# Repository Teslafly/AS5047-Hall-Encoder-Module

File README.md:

# AS5047-Hall-Encoder-Module
Mini breakout Board for the AS5047 Hall Encoder chip. Works with Vesc

this project is made with kicad nightly 5.99. if it doesn't open with the latest kicad version, it will with `Version: (5.99.0-9885-g7a8abcadd2), release build`

!!readme not finished!!

pcb manufacture:
jlcpcbb did a good job and was able to route out the pcb's without mousebites or such.

bom:
digikey/mouser:

lcsc:

conneccctors:
make your own cable:

recommended crimpers:

lcsc connectors:

digikey/mouser connectors:

6 pin cable:
https://www.ebay.com/itm/184222360204?var=691936123738

if you hate crimping, there are prebuilt pigtails you can use to make short runs or cut up to make your own cable.
prebuilt pigtail source:
https://www.ebay.com/itm/114555495221?hash=item1aac0a2335:g:jwIAAOSwGsVaQia0
https://www.aliexpress.com/item/4000699606111.html

(need jst ph source)

# mounting:
 I recommend using nylon m3 screws. like ((xxlinkxxx)). steel screws may disrupt the magnetic feild and affect sensing. they also are non conductive and non marring. while the pcb has been designed to route signals away from under both sides of the screw holes, ther copper ground plane is still present under the screws. screws can be mounted from either side of the board. if mounting directly to metal, it is recommended to put a nylon washer or other piece of plastic between the metal and pcb.

if you have access to a 3d printer. designing a 3d printed mount for this board is likely the easiest route if there is nalready not a good mounting loccation.
provide a example 3d printed mount for each side?

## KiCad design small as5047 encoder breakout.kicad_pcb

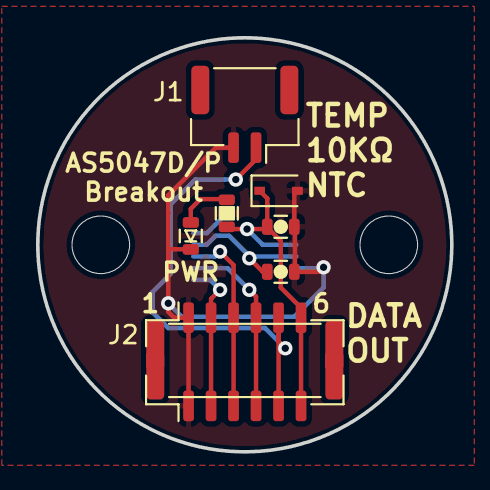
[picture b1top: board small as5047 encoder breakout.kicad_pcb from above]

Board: 2 copper layers, 23.0 x 23.0 mm, 11 parts (1 on the bottom side), 7 nets.

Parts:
C1: 4.7uF; C_0603
C2: 1uF; C_0603
D1: BLUE LED; D_0603
D2: SD05-01FTG; D_SOD-323
H1, H2: MountingHole; MountingHole_3.2mm_M3
J1: Conn_01x02; JST_GH_SM02B-GHS-TB_1x02-1MP_P1.25mm_Horizontal
J2: Conn_01x06; JST_GH_BM06B-GHS-TBT_1x06-1MP_P1.25mm_Vertical
J3: Conn_01x06; JST_GH_SM06B-GHS-TB_1x06-1MP_P1.25mm_Horizontal
R1: 10K; R_0603
U1: AS5047P; TSSOP-14_4.4x5mm_P0.65mm

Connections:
+3V3: C2.1, U1.4 (MOSI), U1.12 (VDD3V3)
+5V: C1.1, D2.1 (K), J2.6, J3.6, R1.1, U1.11 (VDD)
/H1/SCK: J2.4, J3.4, U1.2 (CLK)
/H2/MISO: J2.3, J3.3, U1.3 (MISO)
/H3/CS: J2.2, J3.2, U1.1 (~CS)
/Temp: J1.1, J2.5, J3.5
GND: C1.2, C2.2, D2.2 (A), J1.2, J2.1, J3.1, U1.5 (TST), U1.13 (GND)

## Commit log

2021-05-16 full working pcb
2021-05-16 add readme links
2021-05-16 update readme with photos
